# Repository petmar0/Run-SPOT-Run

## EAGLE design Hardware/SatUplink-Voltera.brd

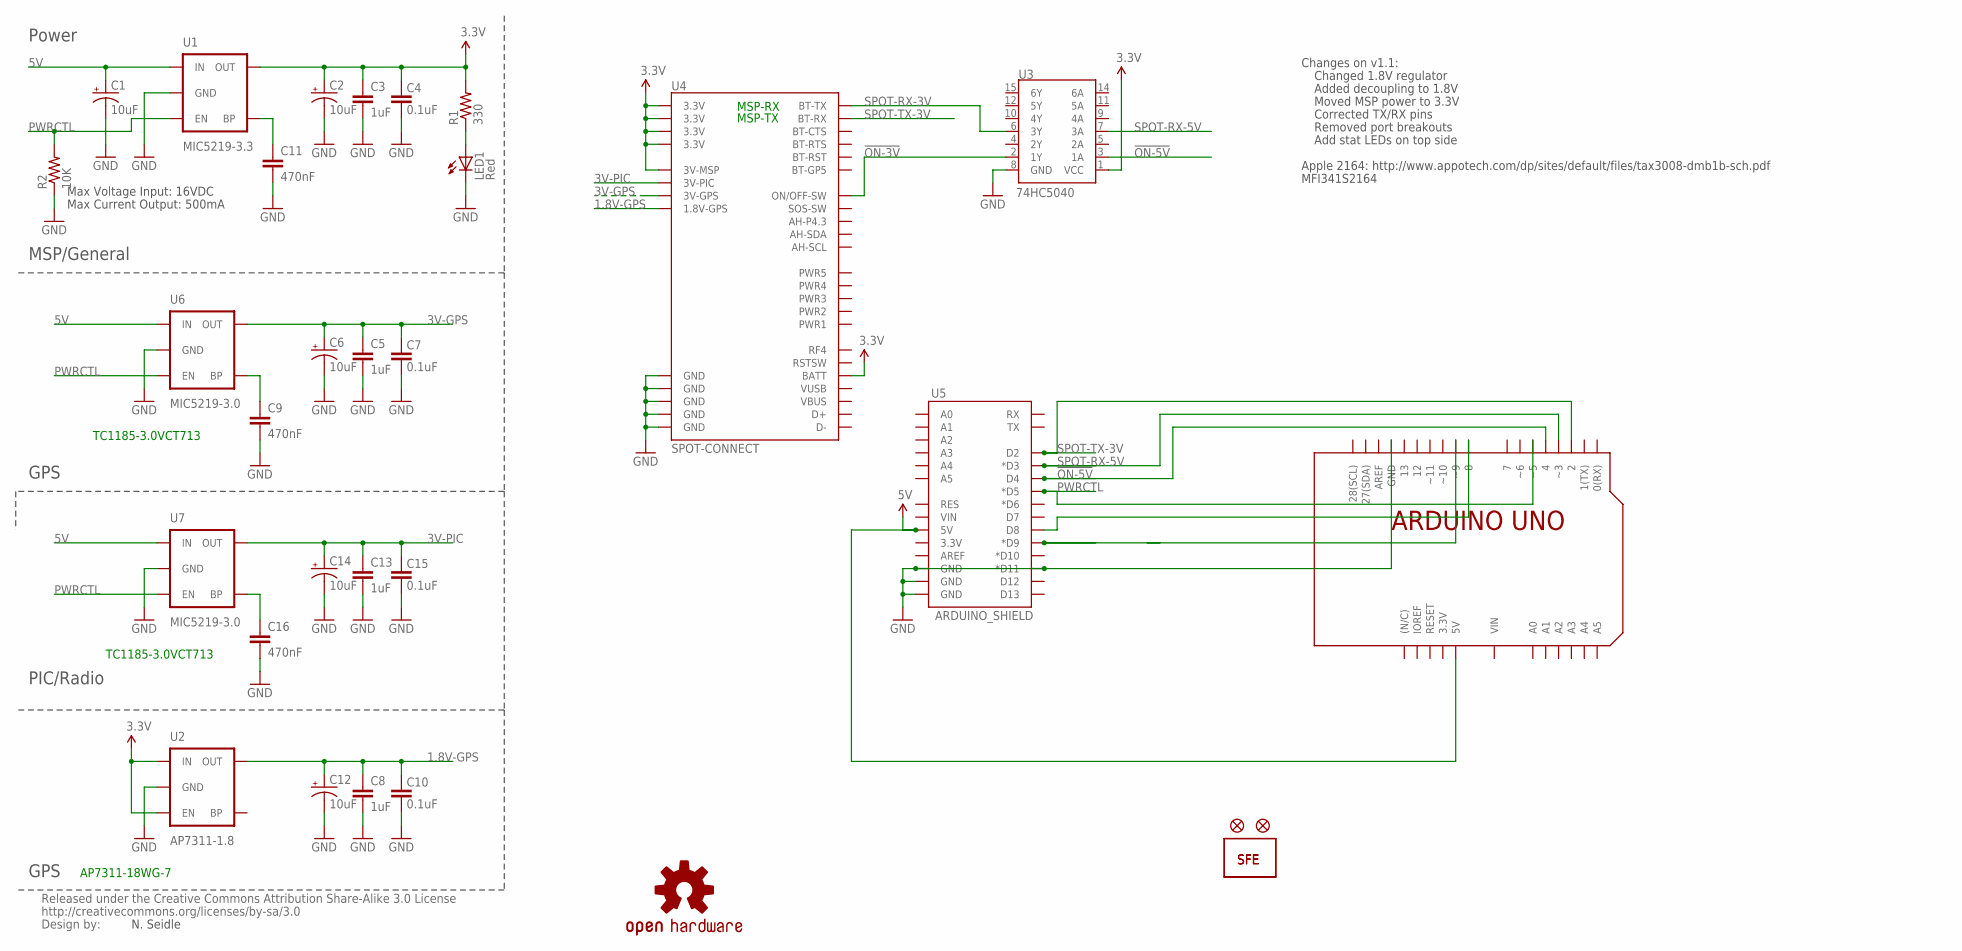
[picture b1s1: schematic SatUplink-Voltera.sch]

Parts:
C1, C2, C6, C12, C14: 10uF; EIA3216
C3, C5, C8, C13: 1uF; 0402-CAP
C4, C7, C10, C15: 0.1uF; 0402-CAP
C9, C11, C16: 470nF; 0402-CAP
JP10, JP11: FIDUCIALUFIDUCIAL; MICRO-FIDUCIAL
LED1: Red; LED-0603
R1: 330; 0402-RES
R2: 10K; 0402-RES
U1: MIC5219-3.3; SOT23-5
U2: AP7311-1.8; SOT23-5
U3: 74HC5040; SO016
U4: SPOT-CONNECT
U5: ARDUINO_SHIELD; DUEMILANOVE_VIAS
U6, U7: MIC5219-3.0; SOT23-5
U$1: LOGO-SFESK; SFE-LOGO-FLAME
U$2: CREATIVE_COMMONS
U$3: OSHW-LOGOS; OSHW-LOGO-S
U$4: TEMPLATE_ARDUINO_UNO_SHIELD; ARDUINO_UNO
U$11: LOGO-SFENEW; SFE-NEW-WEBLOGO

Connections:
1.8V-GPS: C8.1, C10.2, C12.A (+), U2.5 (OUT), U4.1.8V-GPS
3.3V: C2.A (+), C3.1, C4.2, R1.2, U1.5 (OUT), U2.1 (IN), U2.3 (EN), U3.1 (VCC), U4.3.3V@1 (3.3V), U4.3.3V@2 (3.3V), U4.3.3V@3 (3.3V), U4.3.3V@4 (3.3V), U4.3VMSP (3V-MSP), U4.BATT
3V-GPS: C5.1, C6.A (+), C7.2, U4.3V-GPS, U6.5 (OUT)
3V-PIC: C13.1, C14.A (+), C15.2, U4.3VPIC (3V-PIC), U7.5 (OUT)
5V: C1.A (+), U1.1 (IN), U5.5V, U6.1 (IN), U7.1 (IN), U$4.5V@1 (5V), U$4.5V@2 (5V)
!ON-3V: U3.2 (1Y), U4.ON/OFF (ON/OFF-SW)
!ON-5V: U3.3 (1A), U5.D4, U$4.4@1 (4), U$4.4@2 (4)
GND: C1.C (-), C2.C (-), C3.2, C4.1, C5.2, C6.C (-), C7.1, C8.2, C9.2, C10.1, C11.2, C12.C (-), C13.2, C14.C (-), C15.1, C16.2, LED1.C, R2.1, U1.2 (GND), U2.2 (GND), U3.8 (GND), U4.GND@1 (GND), U4.GND@2 (GND), U4.GND@3 (GND), U4.GND@4 (GND), U4.GND@5 (GND), U5.D11 (*D11), U5.GND@0 (GND), U5.GND@1 (GND), U5.GND@2 (GND), U6.2 (GND), U7.2 (GND), U$4.GND..@1 (GND), U$4.GND..@2 (GND), U$4.GND.@1 (GND), U$4.GND.@2 (GND), U$4.GND@1 (GND), U$4.GND@2 (GND)
unnamed: C16.1, U7.4 (BP)
unnamed: C9.1, U6.4 (BP)
unnamed: U5.D8, U$4.8@1 (8), U$4.8@2 (8)
unnamed: U5.D9 (*D9), U$4.9@1 (~9), U$4.9@2 (~9)
unnamed: C11.1, U1.4 (BP)
unnamed: LED1.A, R1.1
PWRCTL: R2.2, U1.3 (EN), U5.D5 (*D5), U6.3 (EN), U7.3 (EN), U$4.5@1 (~5), U$4.5@2 (~5)
SPOT-RX-3V: U3.6 (3Y), U4.BT-TX
SPOT-RX-5V: U3.7 (3A), U5.D3 (*D3), U$4.3@1 (~3), U$4.3@2 (~3)
SPOT-TX-3V: U4.BT-RX, U5.D2, U$4.2@1 (2), U$4.2@2 (2)

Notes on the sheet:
Max Voltage Input: 16VDC
Max Current Output: 500mA
N. Seidle
TC1185-3.0VCT713
Add stat LEDs on top side
Apple 2164: http://www.appotech.com/dp/sites/default/files/tax3008-dmb1b-sch.pdf
MFI341S2164
MSP-TX
MSP-RX
AP7311-18WG-7
Changes on v1.1:
Added decoupling to 1.8V
Changed 1.8V regulator
Moved MSP power to 3.3V
Corrected TX/RX pins
Removed port breakouts
PIC/Radio
GPS
MSP/General
Power

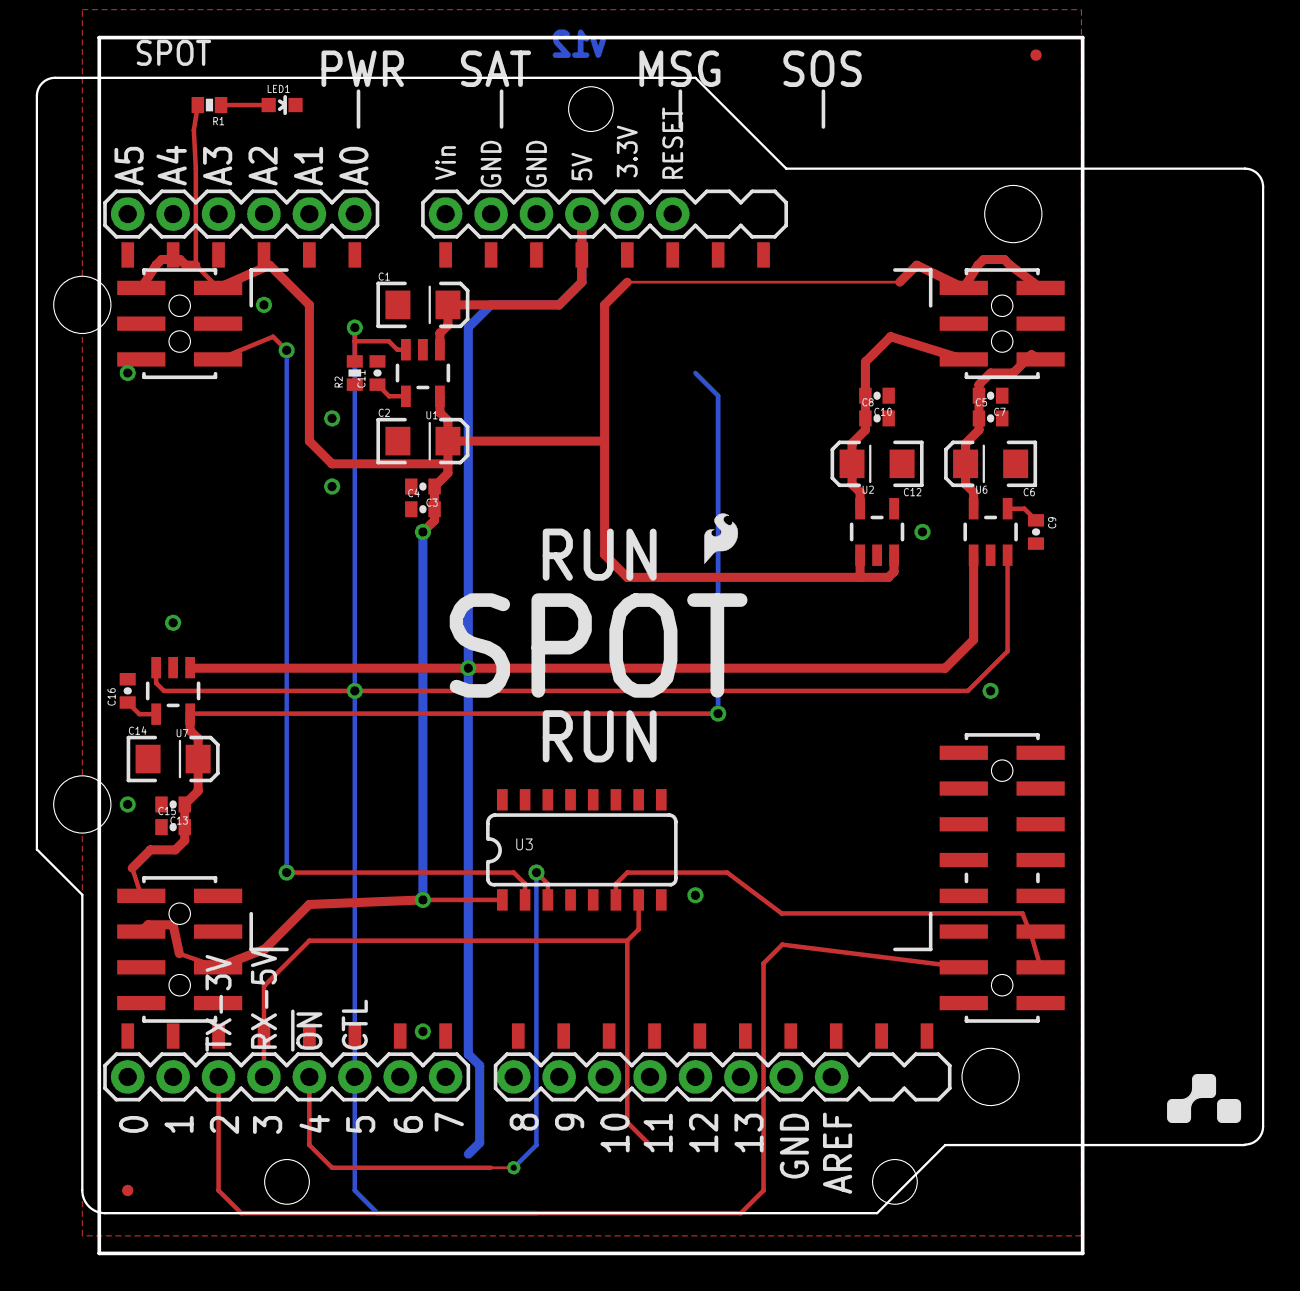
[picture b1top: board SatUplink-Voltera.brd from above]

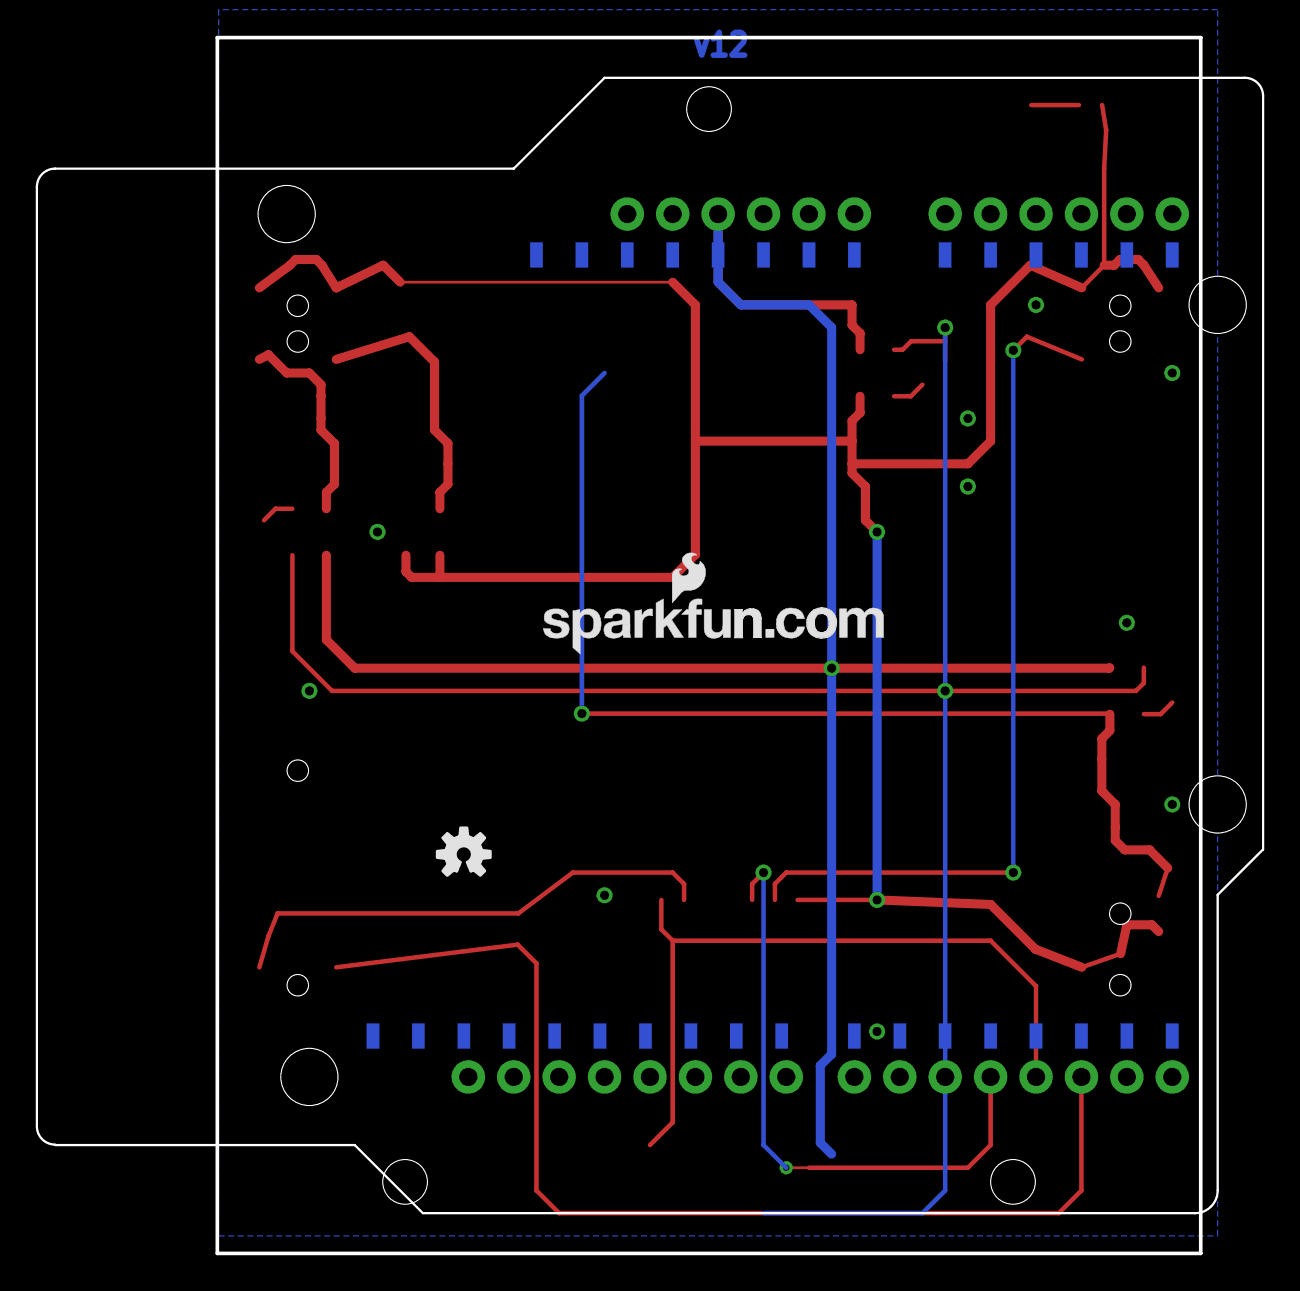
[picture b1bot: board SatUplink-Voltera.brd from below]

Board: 4 copper layers, 68.5 x 68.0 mm, 33 parts (2 on the bottom side), 18 nets.

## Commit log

2017-07-07 Voltera Edits
    The V12 board has been edited to fit onto the Voltera Arduino Uno
    substrate board.

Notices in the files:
parts and their libraries:
SparkFun: Released under the Creative Commons Attribution Share-Alike 3.0 License
SparkFun: http://creativecommons.org/licenses/by-sa/3.0
